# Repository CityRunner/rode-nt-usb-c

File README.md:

# USB-C Mod for RØDE NT-USB Microphone

Drop-in USB-C daughterboard for the RØDE NT-USB microphone, replacing the original USB-B port.

Designed to fit inside the existing housing - no modification required.
Includes a power LED visible through a transparent 3D-printed insert.
All components are 1206 SMD for easy hand soldering and compact layout.

Watch step-by-step installation on [YouTube:](https://www.youtube.com/embed/nsAjaJf2-Ug)

## Features

- **USB-C Connector**: 16-pin edge-mount receptacle.
- **Power Indicator**: Red LED with 220 Ω current-limiting resistor.
- **CC Biasing**: Two 5.11 kΩ pull-down resistors for host detection.

❗**Note:** Tested with the original shielded RØDE SC18 USB-A to USB-C cable. Using cheap USB cables may cause additional noise.

## Images

## Component List:

| Reference | Qty | Value                            | Digikey Number               |
|-----------|-----|----------------------------------|------------------------------|
| D1        | 1   | LED RED CLEAR 1206 SMD           | 754-APTR3216SECK/J3-PRVCT-ND |
| J1        | 1   | CONN RCP USB2.0 TYP C 24P SMD RA | 2073-USB4105-GF-ACT-ND       |
| J2        | 1   | CONN BRD STACK 2.00 40POS        | 612-TW-40-11-S-S-170-100-ND  |
| R1        | 1   | RES 220 OHM 1% 1/4W 1206         | 311-220FRCT-ND               |
| R2, R3    | 2   | RES 5.11K OHM 1% 1/4W 1206       | RMCF1206FT5K11CT-ND          |

❗**Important:** The J2 connector must be **exactly** this size (mm):

- **Pitch:** 2.00
- **Length:**
  - **Overall:** 10.08
  - **Post:** 3.22
  - **Stack:** 4.31
  - **Tail:** 2.54

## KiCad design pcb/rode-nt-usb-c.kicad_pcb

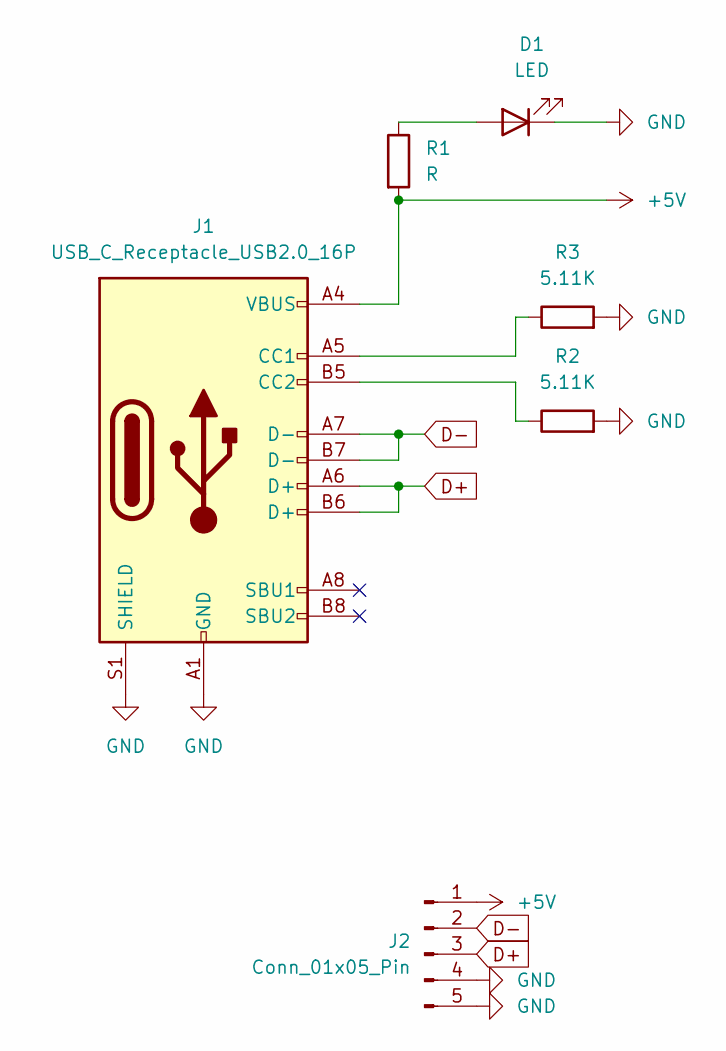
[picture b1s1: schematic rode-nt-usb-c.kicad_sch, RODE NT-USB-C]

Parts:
D1: LED; LED_1206_3216Metric_Pad1.42x1.75mm_HandSolder
J1: USB_C_Receptacle_USB2.0_16P; USB_C_Receptacle_GCT_USB4105-xx-A_16P_TopMnt_Horizontal
J2: Conn_01x05_Pin; PinHeader_1x05_P2.00mm_Vertical
R1: R; R_1206_3216Metric_Pad1.30x1.75mm_HandSolder
R2, R3: 5.11K; R_1206_3216Metric_Pad1.30x1.75mm_HandSolder

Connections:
+5V: J1.A4 (VBUS), J1.A9 (VBUS), J1.B4 (VBUS), J1.B9 (VBUS), J2.1, R1.2
D+: J1.A6 (D+), J1.B6 (D+), J2.3
D-: J1.A7 (D-), J1.B7 (D-), J2.2
GND: D1.1 (K), J1.A1 (GND), J1.A12 (GND), J1.B1 (GND), J1.B12 (GND), J1.S1 (SHIELD), J2.4, J2.5, R2.2, R3.2
unnamed: D1.2 (A), R1.1
unnamed: J1.A5 (CC1), R3.1
unnamed: J1.B5 (CC2), R2.1

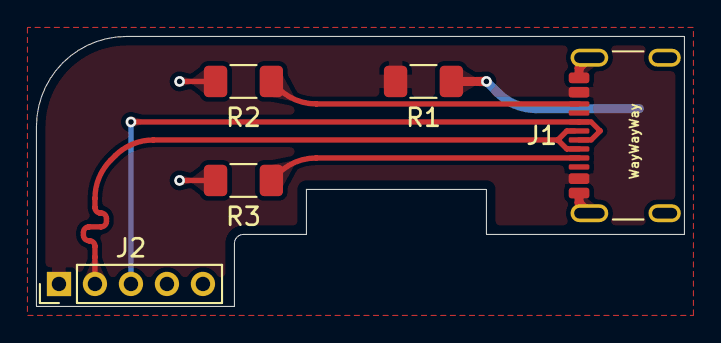
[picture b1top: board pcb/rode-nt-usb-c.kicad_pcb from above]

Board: 2 copper layers, 36.0 x 15.0 mm, 6 parts (1 on the bottom side), 7 nets.

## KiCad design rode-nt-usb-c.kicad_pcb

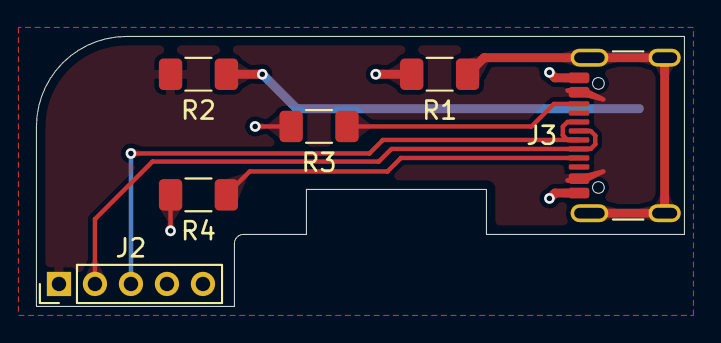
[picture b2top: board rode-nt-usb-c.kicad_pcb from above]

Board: 2 copper layers, 36.0 x 15.0 mm, 7 parts (1 on the bottom side), 8 nets.

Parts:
D1: LED; LED_1206_3216Metric_Pad1.42x1.75mm_HandSolder
J2: Conn_01x05_Pin; PinHeader_1x05_P2.00mm_Vertical
J3: USB_C_Receptacle_USB2.0_16P; USB_C_Receptacle_GCT_USB4105-xx-A_16P_TopMnt_Horizontal
R1: 1M; R_1206_3216Metric_Pad1.30x1.75mm_HandSolder
R2: R; R_1206_3216Metric_Pad1.30x1.75mm_HandSolder
R3, R4: 5.11K; R_1206_3216Metric_Pad1.30x1.75mm_HandSolder

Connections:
+5V: J2.1, J3.A4 (VBUS), J3.A9 (VBUS), J3.B4 (VBUS), J3.B9 (VBUS), R2.2
D+: J2.3, J3.A6 (D+), J3.B6 (D+)
D-: J2.2, J3.A7 (D-), J3.B7 (D-)
GND: D1.1 (K), J2.4, J2.5, J3.A1 (GND), J3.A12 (GND), J3.B1 (GND), J3.B12 (GND), R1.2, R3.2, R4.2
unnamed: D1.2 (A), R2.1
unnamed: J3.A5 (CC1), R4.1
unnamed: J3.B5 (CC2), R3.1
unnamed: J3.S1 (SHIELD), R1.1

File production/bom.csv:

Designator,Footprint,Quantity,Value,LCSC Part #
D1,1206,1,LED,
J1,USB_C_Receptacle_GCT_USB4105-xx-A_16P_TopMnt_Horizontal,1,USB_C_Receptacle_USB2.0_16P,
J2,PinHeader_1x05_P2.00mm_Vertical,1,Conn_01x05_Pin,
R1,1206,1,1M,
R2,1206,1,R,
"R3, R4",1206,2,5.11K,

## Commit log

2025-03-07 Add project files
2025-03-09 Mod pcb for plastic insert
2025-03-10 Change cutouts
2025-03-10 Add LED, reroute
2025-03-11 Change routing
2025-03-12 Add description
2025-03-12 Add images
2025-03-12 edit readme
2025-03-13 Change usb side
2025-03-13 Add 3d insert model, change pcb
2025-03-13 rearrange files
2025-03-13 change readme
2025-03-14 Change size
2025-03-14 Add production files
2025-04-27 Remove R1, update overall design
2025-04-27 Change design, multiple adjustments
2025-04-27 Minor adjustments
2025-04-27 Adjust size
2025-04-30 Update design
2025-04-30 Updates production files, misc
2026-02-14 Adjust pcb net
